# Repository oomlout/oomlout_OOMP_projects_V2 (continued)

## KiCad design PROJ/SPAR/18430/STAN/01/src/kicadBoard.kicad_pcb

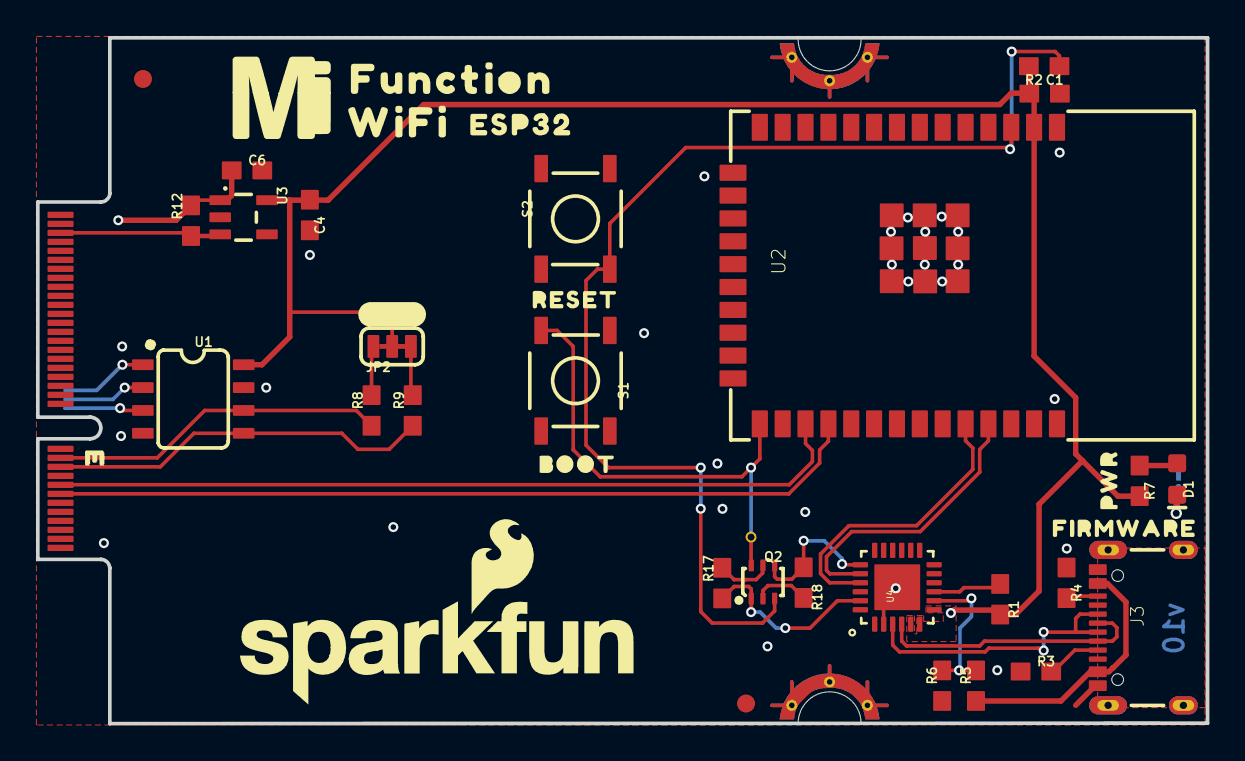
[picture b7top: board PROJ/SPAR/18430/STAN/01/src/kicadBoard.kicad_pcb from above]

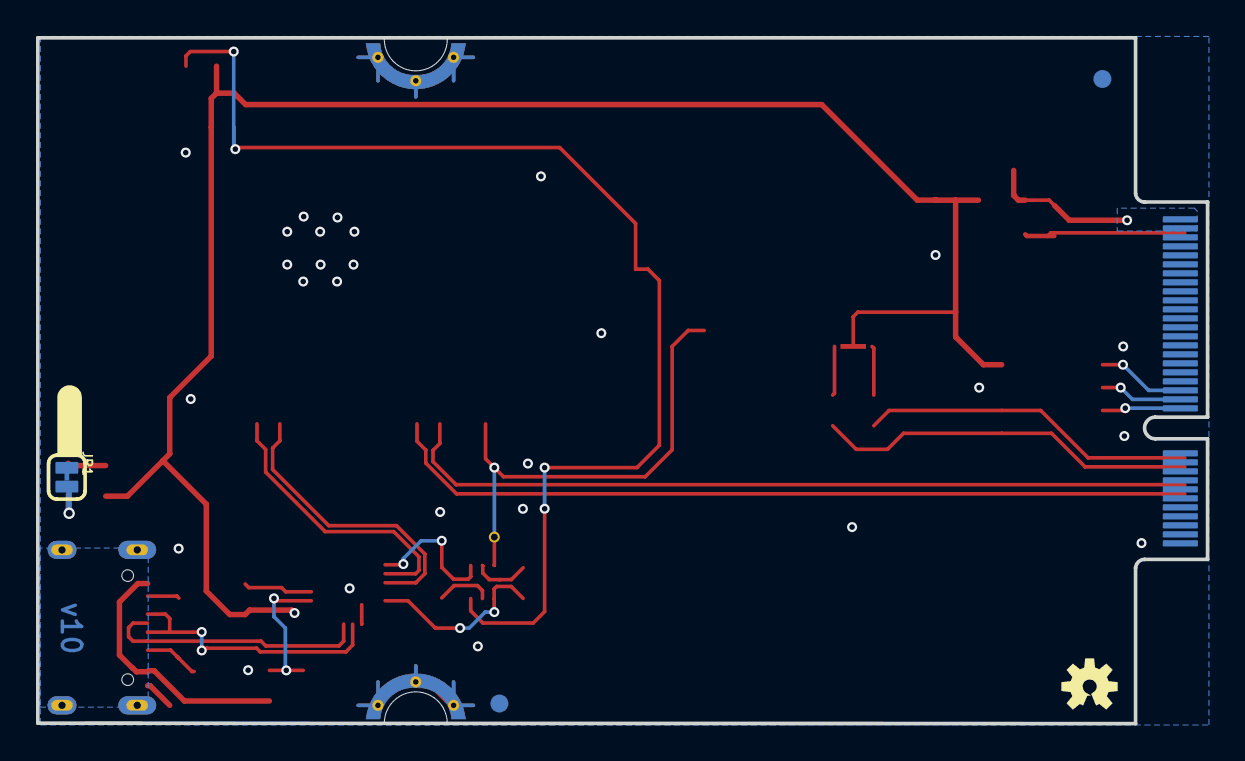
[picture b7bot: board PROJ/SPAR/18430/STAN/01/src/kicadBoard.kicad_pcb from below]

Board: 2 copper layers, 65.0 x 38.1 mm, 46 parts (5 on the bottom side), 31 nets.

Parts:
C1: 0.1uF; 0603
C4, C6: 1.0uF; 0603
D1: RED; LED-0603
FD1, FD2, FD3, FD4: FIDUCIAL1X2; FIDUCIAL-1X2
FRAME2: FRAME-LEDGER; CREATIVE_COMMONS
J1: MICROMOD_FUNCTION_STANDARD; M.2-CARD-E-22_FUNCTION_STANDARD
J3: USB-C-16P-2LAYER-PADS
JP1: JUMPER-SMT_2_NC_TRACE_SILK; SMT-JUMPER_2_NC_TRACE_SILK
JP2: JUMPER-SMT_3_2-NC_TRACE_SILK; SMT-JUMPER_3_2-NC_TRACE_SILK
LOGO1: SPECIAL_INSTRUCTIONS-ORDERING; ORDERING_INSTRUCTIONS
LOGO2: SFE_LOGO_NAME_FLAME.2_INCH; SFE_LOGO_NAME_FLAME_.2
LOGO3: OSHW-LOGOS; OSHW-LOGO-S
Q2: MBT3904DW1T1; SC70-6
R1, R2, R17, R18: 10k; 0603
R3, R4: 5.1k; 0603
R5: 22k; 0603
R6: 33k; 0603
R7: 1k; 0603
R8, R9: 4.7k; 0603
R12: 100k; 0603
S1, S2: MOMENTARY-SWITCH-SPST-SMD-5.2MM-TALL; TACTILE_SWITCH_SMD_5.2MM
TP2: TEST-POINTTP_15TH_THRU; TP_15TH
U1: EEPROM; SO08
U2: ESP-WROOM-3232D-NARROW; ESP-WROOM-32D-NARROW
U3: 3.3V; SOT23-5
U4: CP210X; QFN24
U$1: BOOT3221
U$2: FUNCTION521
U$3: #I2C#1321540313558
U$4: ESP3212
U$5: RESET3220
U$6: MICROMOD_MI_LOGO_1
U$7: FIRMWARE3223
U$8: #LED#8
U$9: PWR3215
U$10: WIFI525

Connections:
0: Q2.6, S1.3, TP2.1, U2.25
3.3V: C1.1, C4.1, JP2.2, R1.2, R2.2, R7.2, U1.8, U2.2, U3.5, U4.5, U4.6, U4.7
16/RX: J1.15, U2.27
17/TX: J1.13, U2.28
CHIP_PU: Q2.3, R2.1, S2.3, U2.3
D+: J3.A6, J3.B6, U4.3
D-: J3.A7, J3.B7, U4.4
DTR: Q2.1, R17.1, U4.23
EN: J1.71, R12.1, U3.3
GND: C1.2, C4.2, C6.2, J1.1, J1.33, J1.39, J1.45, J1.75, J1.GND1, J1.GND2, J1.GND3, J1.GND4, J1.GND5, J1.GND6, J3.GND, J3.GND2, JP1.1, R3.1, R4.1, R6.1, S1.1, S2.1, U1.4, U1.7, U2.1, U2.15, U2.38, U2.GND1, U2.GNDT1, U2.GNDT2, U2.GNDT3, U2.GNDT4, U2.GNDT5, U2.GNDT6, U2.GNDT7, U2.GNDT8, U3.2, U4.2, U4.PAD
I2C_SCL: J1.21, R8.1, U1.6
I2C_SDA: J1.19, R9.1, U1.5
unnamed: R1.1, U4.9
unnamed: J3.A5, R3.2
unnamed: J3.VBUS1, J3.VBUS2, R5.1
unnamed: R5.2, R6.2, U4.8
unnamed: J3.B5, R4.2
unnamed: D1.C, JP1.2
unnamed: D1.A, R7.1
unnamed: J1.32, U1.3
unnamed: J1.34, U1.2
unnamed: Q2.5, R17.2
unnamed: J1.36, U1.1
unnamed: Q2.2, R18.2
unnamed: JP2.1, R9.2
unnamed: JP2.3, R8.2
RTS: Q2.4, R18.1, U4.19
RX: U2.35, U4.20
SHLD: J3.SHLD1, J3.SHLD2, J3.SHLD3, J3.SHLD4
TX: U2.34, U4.21
VCC: C6.1, J1.72, J1.74, R12.2, U3.1

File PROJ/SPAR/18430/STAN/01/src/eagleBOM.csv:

"Part";"Value";"Device";"Package";"Description";"DESIGNER";"PROD_ID";"REV";"VALUE";
"C1";"0.1uF";"0.1UF-0603-25V-(+80/-20%)";"0603";"0.1µF ceramic capacitors";"";"CAP-00810";"";"0.1uF";
"C4";"1.0uF";"1.0UF-0603-16V-10%";"0603";"1µF ceramic capacitors";"";"CAP-00868";"";"1.0uF";
"C6";"1.0uF";"1.0UF-0603-16V-10%";"0603";"1µF ceramic capacitors";"";"CAP-00868";"";"1.0uF";
"D1";"RED";"LED-RED0603";"LED-0603";"Red SMD LED";"";"DIO-00819";"";"RED";
"FD1";"FIDUCIAL1X2";"FIDUCIAL1X2";"FIDUCIAL-1X2";"Fiducial Alignment Points";"";"";"";"";
"FD2";"FIDUCIAL1X2";"FIDUCIAL1X2";"FIDUCIAL-1X2";"Fiducial Alignment Points";"";"";"";"";
"FD3";"FIDUCIAL1X2";"FIDUCIAL1X2";"FIDUCIAL-1X2";"Fiducial Alignment Points";"";"";"";"";
"FD4";"FIDUCIAL1X2";"FIDUCIAL1X2";"FIDUCIAL-1X2";"Fiducial Alignment Points";"";"";"";"";
"FRAME2";"FRAME-LEDGER";"FRAME-LEDGER";"CREATIVE_COMMONS";"Schematic Frame - Ledger";"";"";"";"";
"J1";"MICROMOD_FUNCTION_STANDARD";"MICROMOD_FUNCTION_STANDARD";"M.2-CARD-E-22_FUNCTION_STANDARD";"MicroMod Connector";"";"";"";"";
"J3";"";"USB_C_2-LAYER_PADS";"USB-C-16P-2LAYER-PADS";"USB Type C 16Pin Connector";"";"CONN-14122";"";"";
"JP1";"JUMPER-SMT_2_NC_TRACE_SILK";"JUMPER-SMT_2_NC_TRACE_SILK";"SMT-JUMPER_2_NC_TRACE_SILK";"Normally closed trace jumper";"";"";"";"";
"JP2";"JUMPER-SMT_3_2-NC_TRACE_SILK";"JUMPER-SMT_3_2-NC_TRACE_SILK";"SMT-JUMPER_3_2-NC_TRACE_SILK";"Normally closed trace jumper (2 of 2 connections)";"";"";"";"";
"LOGO1";"SPECIAL_INSTRUCTIONS-ORDERING";"SPECIAL_INSTRUCTIONS-ORDERING";"ORDERING_INSTRUCTIONS";"Special Ordering/Production Instructions Alert";"";"";"";"";
"LOGO2";"SFE_LOGO_NAME_FLAME.2_INCH";"SFE_LOGO_NAME_FLAME.2_INCH";"SFE_LOGO_NAME_FLAME_.2";"SparkFun Font Logo w/ Flame";"";"";"";"";
"LOGO3";"OSHW-LOGOS";"OSHW-LOGOS";"OSHW-LOGO-S";"Open-Source Hardware (OSHW) Logo";"";"";"";"";
"Q2";"MBT3904DW1T1";"TRANS_NPN_DUAL-MBT3904DW1T1";"SC70-6";"Dual NPN Transistors in Single Package";"";"TRANS-13337";"";"";
"R1";"10k";"10KOHM-0603-1/10W-1%";"0603";"10kΩ resistor";"";"RES-00824";"";"10k";
"R2";"10k";"10KOHM-0603-1/10W-1%";"0603";"10kΩ resistor";"";"RES-00824";"";"10k";
"R3";"5.1k";"5.1KOHM5.1KOHM-0603-1/10W-1%";"0603";"";"";"RES-12083";"";"5.1k";
"R4";"5.1k";"5.1KOHM5.1KOHM-0603-1/10W-1%";"0603";"";"";"RES-12083";"";"5.1k";
"R5";"22k";"22KOHM-0603-1/10W-1%";"0603";"22kΩ resistor";"";"RES-07853";"";"22k";
"R6";"33k";"33KOHM-0603-1/10W-1%";"0603";"33kΩ resistor";"";"RES-08416";"";"33k";
"R7";"1k";"1KOHM-0603-1/10W-1%";"0603";"1kΩ resistor";"";"RES-07856";"";"1k";
"R8";"4.7k";"4.7KOHM-0603-1/10W-1%";"0603";"4.7kΩ resistor";"";"RES-07857";"";"4.7k";
"R9";"4.7k";"4.7KOHM-0603-1/10W-1%";"0603";"4.7kΩ resistor";"";"RES-07857";"";"4.7k";
"R12";"100k";"100KOHM-0603-1/10W-1%";"0603";"100kΩ resistor";"";"RES-07828";"";"100k";
"R17";"10k";"10KOHM-0603-1/10W-1%";"0603";"10kΩ resistor";"";"RES-00824";"";"10k";
"R18";"10k";"10KOHM-0603-1/10W-1%";"0603";"10kΩ resistor";"";"RES-00824";"";"10k";
"S1";"MOMENTARY-SWITCH-SPST-SMD-5.2MM-TALL";"MOMENTARY-SWITCH-SPST-SMD-5.2MM-TALL";"TACTILE_SWITCH_SMD_5.2MM";"Momentary Switch (Pushbutton) - SPST";"";"SWCH-14139";"";"";
"S2";"MOMENTARY-SWITCH-SPST-SMD-5.2MM-TALL";"MOMENTARY-SWITCH-SPST-SMD-5.2MM-TALL";"TACTILE_SWITCH_SMD_5.2MM";"Momentary Switch (Pushbutton) - SPST";"";"SWCH-14139";"";"";
"TP2";"TEST-POINTTP_15TH_THRU";"TEST-POINTTP_15TH_THRU";"TP_15TH";"SparkFun Test Points";"";"";"";"";
"U1";"EEPROM";"EEPROM-I2C512K";"SO08";"I2C EEPROMs, 24LC256 and others";"";"IC-14645";"";"";
"U2";"ESP-WROOM-3232D-NARROW";"ESP-WROOM-3232D-NARROW";"ESP-WROOM-32D-NARROW";"ESP-WROOM-32D - trace antenna (includes keepout)";"";"IC-15676";"";"";
"U3";"3.3V";"V_REG_AP2112K-3.3V";"SOT23-5";"AP2112 - 600mA CMOS LDO Regulator w/ Enable";"";"VREG-12457";"";"3.3V";
"U4";"CP210X";"CP2102N";"QFN24";"";"";"IC-14020";"";"";

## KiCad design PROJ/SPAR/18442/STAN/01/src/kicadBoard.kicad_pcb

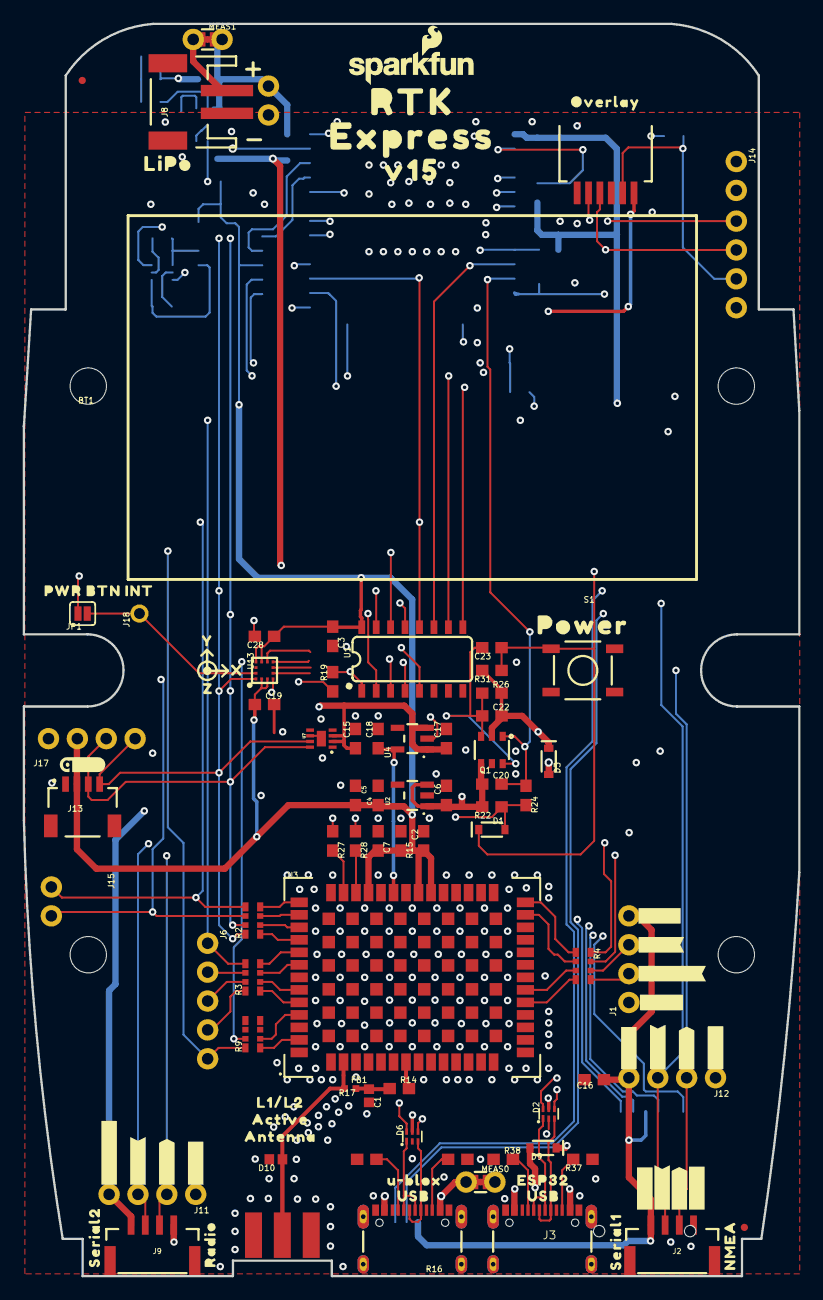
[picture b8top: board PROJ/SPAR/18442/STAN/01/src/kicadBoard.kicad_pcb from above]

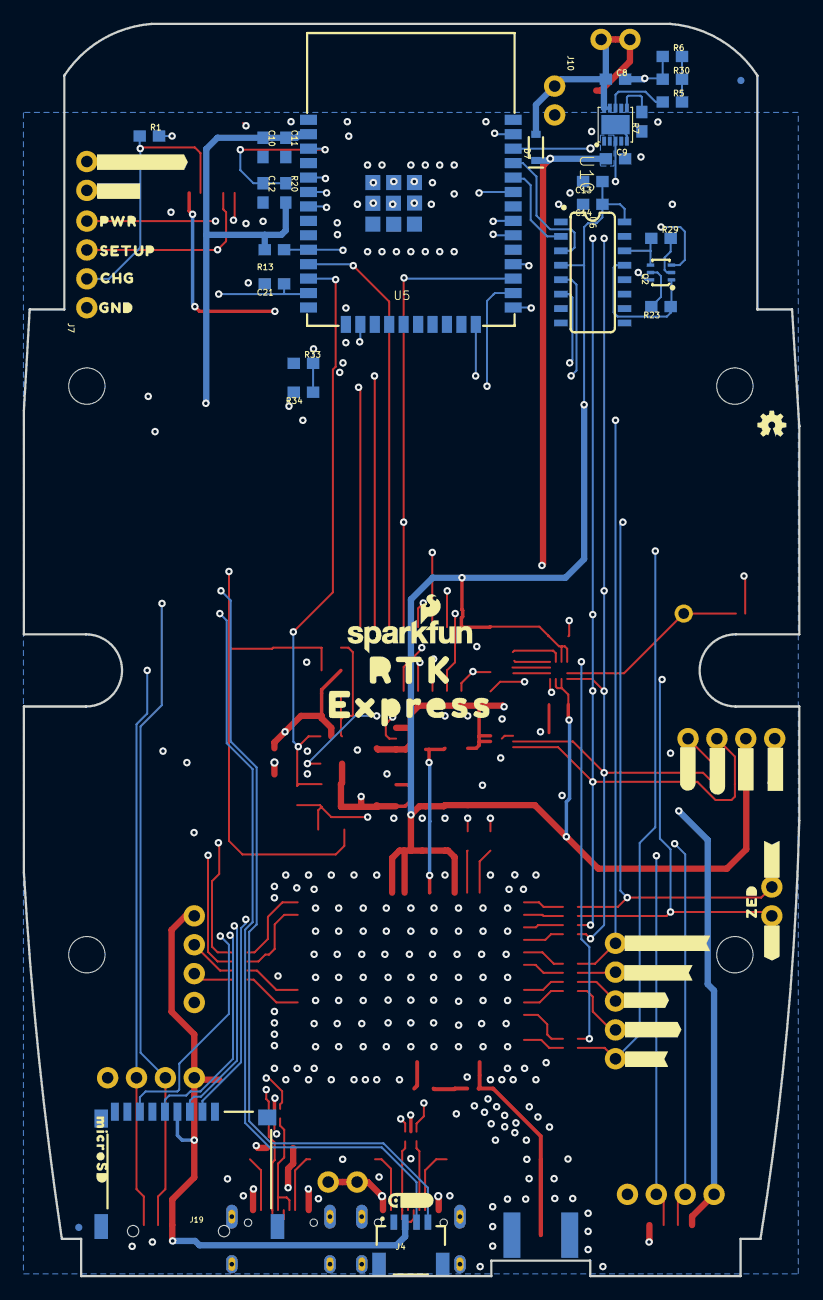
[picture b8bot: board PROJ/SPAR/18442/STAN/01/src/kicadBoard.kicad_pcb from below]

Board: 4 copper layers, 68.2 x 110.1 mm, 168 parts (54 on the bottom side), 86 nets.

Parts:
BT1: LIPO-OUTLINE1000; LIPO-1000
C1: 47pF; 0402
C2, C4, C6, C17, C18: 1.0uF; 0603
C3, C5, C7, C11, C12, C13, C15, C16, C21, C22, C23, C28: 0.1uF; 0603
C8, C9: 4.7uF; 0603
C10, C14, C19, C20: 10uF; 0603
D1: 250mA/100V; SOD-323
D2, D6: PRTR5V0U2F; SOT886
D3, D7, D9: 3A/10V/280mV; SOD-323
D10: PESD0402-0402; 0402
E1: SMA; SMA-EDGE
FB1: 2.66Ω; 0402-TIGHT
FRAME2: FRAME-LEDGER; CREATIVE_COMMONS
FRAME3: FRAME-LEDGERNO_FOOTPRINT; DUMMY
J1, J7, J11, J12: 1X04_NO_SILK
J2, J9: JST-4-SMD-1.25MM-LOCKING
J3, J5: USB Female Type C Connector; USB-C-16P_4LAYER-PADS
J4: Qwiic Right Angle; JST04_1MM_RA
J6: 1X05_NO_SILK
J8: JST-2-SMD
J10, J14, J15: 1X02_NO_SILK
J13: Internal; JST04_1MM_RA
J17: Qwiic Right Angle; 1X04_NO_SILK
J18: 1X01_NO_SILK
J19: MICROSD; MICROSD-EXTERNALPIN
JP1: JUMPER-SMT_2_NO_SILK; SMT-JUMPER_2_NO_SILK
JP2: FPC_6_1MM-LIF
JP21, JP61, JP71, JP81: FIDUCIALUFIDUCIAL; FIDUCIAL-MICRO
LOGO1: OSHW-LOGOMINI; OSHW-LOGO-MINI
LOGO2, LOGO3: SFE_LOGO_NAME_FLAME.1_INCH; SFE_LOGO_NAME_FLAME_.1
MEAS0, MEAS1: COMBO-JUMPER_2_NC_TRACE
Q1: SIL2308-TP; SOT26
Q2: MBT3904DW1T1; SC70-6
R1: 470; 0603
R2, R3, R4, R9: 33; 1206_RA
R5: 0; 0603
R6, R23, R29, R31, R34: 10k; 0603
R7, R19: 1k; 0603
R13, R15, R20, R22, R26: 100k; 0603
R14: 10; 0603
R16, R17, R37, R38: 5.1k; 0603
R24: 300k; 0603
R27, R28: 27; 0603
R30: 150k; 0603
R33: 3.3k; 0603
S1: Power; TACTILE_SWITCH_SMD_5.2MM
U1: 74HC4052D; SO16
U2: AP2112K-3.3; SOT23-5
U3: U-BLOX_ZED-F9P; ZED-F9P
U4: STLQ015-3.3V; SOT23-5
U5: ESP-WROOM-3232D; ESP-WROOM-32D
U6: CH340C; SO016
U7: MAX17048; DFN-8
U10: MCP73833; DFN-10
U13: LIS2DH12; LGA-12-LISDH12
U$1, U$38, U$48, U$82: #GND#0
U$2: SPECIAL_INSTRUCTIONS-ORDERING; ORDERING_INSTRUCTIONS
U$3: #TX_RDY#0
U$4: INT0
U$5, U$37, U$47: #3V3#0
U$6: L1#L20
U$7, U$74: RTK0
U$8: OVERLAY0
U$9: PWR_BTN1
U$10: #RTK#1
U$11: #PPS#0
U$13: ACTIVE1
U$14: #RX#2
U$15: ANTENNA2
U$16: ZED0
U$17: ##SAFE##5
U$18: V150
U$23: #3#5#5V#0
U$24: X0
U$26: 1553DBK-ENCLOSURE
U$27: LIPO0
U$28: ##RST##4
U$29: SERIAL10
U$30, U$93: QWIIC_4MM
U$31: POWER0
U$32: #FENCE#3
U$33: CHG2
U$34: GND3
U$35: U#BLOX0
U$36, U$66: USB1
U$39: #RX2#2
U$40: #TX2#1
U$41: PWR0
U$42: SETUP1
U$43: SERIAL20
U$45, U$68: #RX1#2
U$46, U$65: #TX1#1
U$49: NMEA1
U$50: RADIO0
U$51, U$53: EXPRESS0
U$55: Y1
U$56: Z2
U$60: #ESP_RST#0
U$67: ESP320
U$70: #GND#2
U$72: #TX#1
U$83: MICROSD0
U$84: #GND#1
U$85: #3V3#2
U$86: #SCL#1
U$87: #SDA#0
U$88: #D_SEL#0

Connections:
3.3V: C2.1, C3.1, C4.1, C5.2, C7.2, C10.1, C11.1, C13.1, C14.1, C16.1, C19.1, C28.1, J1.4, J2.1, J4.2, J12.4, J13.2, J17.2, J19.4, R13.2, R15.2, R20.2, R34.2, U1.16, U2.5, U3.33, U3.34, U3.38, U5.2, U6.4, U6.16, U13.2, U13.3, U13.9, U13.10
ANT_VCC: C1.1, FB1.2, R14.1
CC1: J5.A5, R17.2
CC2: J5.B5, R16.2
CC3: J3.B5, R37.2
CC4: J3.A5, R38.2
CHG_LED: R1.2, U10.3
CHG_LED_RES: J7.2, JP2.2, R1.1
CHG_THERM1: R5.2, R6.2, R30.2
D+: D6.4, R27.1
D+1: D2.4, U6.5
D-: D6.6, R28.1
D-1: D2.6, U6.6
ESP32_EN: C12.1, J14.1, Q2.3, R20.1, U5.3
ESP32_RXI: U5.34, U6.2
ESP32_TXO: U5.35, U6.3
ESP32_~DTR: Q2.1, R23.1, U6.13
ESP32_~RTS: Q2.4, R29.1, U6.14
ESP_0/BOOT: Q2.6, U5.25
ESP_2/MUX_A: U1.10, U5.24
ESP_4/ACCEL_INT: J18.1, JP1.1, U13.12
ESP_4/MUX_B: U1.9, U5.26
ESP_13/POWER_CTRL: D1.A, R22.1, R24.2, U5.16
ESP_14/SETUP_BUTTON: C21.1, J7.3, JP2.4, U5.13
ESP_18/SCK: J19.5, U5.30
ESP_19/CIPO: J19.7, U5.31
ESP_21/SDA: J4.3, J13.3, J17.3, R2.P7, U1.2, U5.33, U7.8, U13.4
ESP_22/SCL: J4.4, J13.4, J17.4, R2.P8, U1.15, U5.36, U7.7, U13.1
ESP_23/COPI: J19.3, U5.37
ESP_25/SD_~CS: J19.2, R13.1, U5.10
ESP_26/DAC2: U1.11, U5.11
ESP_26/ZED_TX_READY_LV: R3.P4, U3.46
ESP_27/FAST_OFF: C20.2, Q1.G1, R24.1, U5.12
ESP_D1+: D2.3, J3.A6, J3.B6
ESP_D1-: D2.1, J3.A7, J3.B7
ESP_I16/ZED-TXO1: J15.1, R2.P5, U1.12, U5.27
ESP_I34/ZED_TX_READY: J6.1, R3.P5, U5.6
ESP_I35/DEVICE_SENSE: R33.2, R34.1, U5.7
ESP_I39/ADC39: U1.4, U5.5
ESP_O17/ZED-RXI1: J15.2, R2.P6, R19.2, U1.1
EXTERNAL_DATA_IN: J2.3, J12.2, U1.3
EXTERNAL_DATA_OUT: J2.2, J12.3, U1.13
EXTINT_LV: R9.P2, U3.51
FENCE_LV: R4.P4, U3.19
GND: C1.2, C2.2, C3.2, C4.2, C5.1, C6.2, C7.1, C8.2, C9.2, C10.2, C11.2, C12.2, C13.2, C14.2, C15.2, C16.2, C17.2, C18.2, C19.2, C21.2, C28.2, D2.2, D6.2, D10.2, E1.GND@0, E1.GND@1, E1.GND@2, E1.GND@3, J1.1, J2.4, J3.GND, J3.GND2, J3.SHLD1, J3.SHLD2, J3.SHLD3, J3.SHLD4, J4.1, J5.GND, J5.GND2, J5.SHLD1, J5.SHLD2, J5.SHLD3, J5.SHLD4, J7.1, J8.1, J9.4, J10.2, J11.1, J12.1, J13.1, J14.2, J17.1, J19.6, J19.9, J19.10, J19.11, J19.12, J19.13, JP2.6, Q1.S1, R6.1, R7.1, R15.1, R16.1, R17.1, R30.1, R33.1, R37.1, R38.1, S1.3, U1.6, U1.7, U1.8, U2.2, U3.1, U3.3, U3.12, U3.14, U3.32, U3.37, U3.41, U3.48, U3.55, U3.56, U3.57, U3.58, U3.59, U3.60, U3.61, U3.62, U3.63, U3.64, U3.65, U3.66, U3.67, U3.68, U3.69, U3.70, U3.71, U3.72, U3.73, U3.74, U3.75, U3.76, U3.77, U3.78, U3.79, U3.80, U3.81, U3.82, U3.83, U3.84, U3.85, U3.86, U3.87, U3.88, U3.89, U3.90, U3.91, U3.92, U3.93, U3.94, U3.95, U3.96, U3.97, U3.98, U3.99, U3.100, U3.101, U3.102, U4.2, U5.1, U5.15, U5.38, U5.GND, U5.GNDT1, U5.GNDT2, U5.GNDT3, U5.GNDT4, U5.GNDT5, U5.GNDT6, U5.GNDT7, U5.GNDT8, U6.1, U7.1, U7.4, U7.6, U7.9, U10.5, U10.11, U13.5, U13.6, U13.7, U13.8
GPS_ANT1: D10.1, E1.SIG, FB1.1, U3.2
LIPO_RAW: J8.2, MEAS1.1, MEAS1.3
unnamed: J5.VBUS1, J5.VBUS2, MEAS0.1, MEAS0.3
unnamed: R5.1, U10.8
unnamed: R19.1, U5.28
unnamed: R27.2, U3.40
unnamed: R28.2, U3.39
unnamed: R14.2, U3.7
unnamed: C22.1, C23.2, Q1.D1, Q1.G2, R26.1
unnamed: Q2.5, R23.2
unnamed: Q2.2, R29.2
unnamed: D9.A, J3.VBUS1, J3.VBUS2
POWER_BTN: C23.1, D1.C, J7.4, JP1.2, JP2.5, R31.1, S1.1
PPS: R9.P1, U3.53
PROG1: R7.2, U10.6
RTK_LV: R4.P3, U3.20
RX2_LV: R4.P2, U3.26
RXLV: R2.P3, U3.43
SCL_LV: R2.P1, U3.45
SDA_LV: R2.P2, U3.44
TX2_LV: R4.P1, U3.27
TXLV: R2.P4, U3.42
UNP_D+: D6.3, J5.A6, J5.B6
UNP_D-: D6.1, J5.A7, J5.B7
VOUT: C6.1, C20.1, J9.1, J11.4, Q1.D2, R22.2, U2.1, U2.3
V_BATT: C8.1, C15.1, C17.1, D7.A, J10.1, MEAS1.2, MEAS1.4, U4.1, U4.3, U7.2, U7.3, U10.9, U10.10
V_BKCP: C18.1, U3.36, U4.5
V_RAW: C9.1, C22.2, D3.C, D7.C, Q1.S2, R26.2, R31.2, U10.1, U10.2
V_USB: D2.5, D3.A, D6.5, D9.C, JP2.1, MEAS0.2, MEAS0.4
ZED-RXI2: J9.3, J11.2, R4.P7
ZED-TXO2: J9.2, J11.3, R4.P8
ZED_D_SEL: J6.2, R3.P6
ZED_D_SEL_LV: R3.P3, U3.47
ZED_EXTINT: R9.P7, U1.5
ZED_FENCE_STAT: J1.2, R4.P5
ZED_PPS_STAT: J6.5, R9.P8, U1.14
ZED_RTK_STAT: J1.3, R4.P6
ZED_~RESET: J6.3, R3.P7
ZED_~RESET_LV: R3.P2, U3.49
ZED_~SAFE: J6.4, R3.P8
ZED_~SAFE_LV: R3.P1, U3.50
